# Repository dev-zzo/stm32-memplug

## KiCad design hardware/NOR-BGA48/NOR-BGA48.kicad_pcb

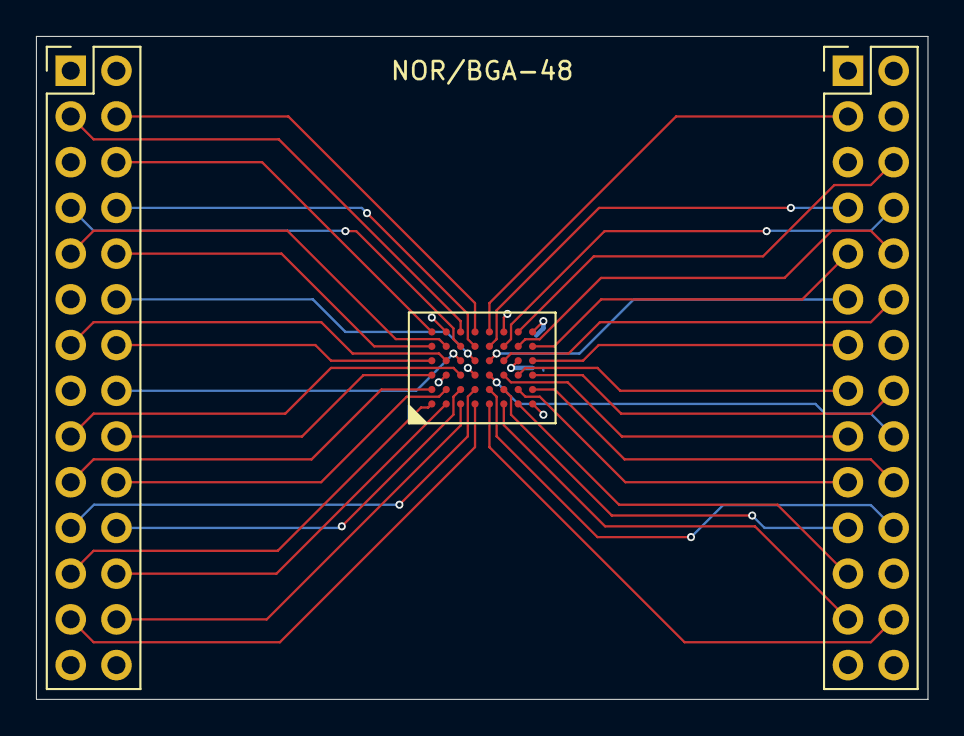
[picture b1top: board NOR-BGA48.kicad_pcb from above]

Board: 4 copper layers, 49.5 x 36.8 mm, 4 parts (1 on the bottom side), 45 nets.

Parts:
C1: 100n; C_0805_2012Metric
J1: Left; PinHeader_2x14_P2.54mm_Vertical
J2: Right; PinHeader_2x14_P2.54mm_Vertical
U1: Generic_NOR_BGA48; BGA48C80P8X6_815X615X100

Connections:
+3V3: C1.1, J2.14, J2.28, U1.B3, U1.F6, U1.G4
A0: J2.26, U1.E1
A1: J1.25, U1.D1
A2: J1.26, U1.C1
A3: J1.23, U1.A1
A4: J1.24, U1.B1
A5: J1.21, U1.D2
A6: J1.22, U1.C2
A7: J1.19, U1.A2
A8: J1.9, U1.B5
A9: J1.10, U1.A5
A10: J1.7, U1.C5
A11: J1.8, U1.D5
A12: J1.5, U1.B6
A13: J1.6, U1.A6
A14: J1.3, U1.C6
A15: J1.4, U1.D6
A16: J2.3, U1.E6
A17: J1.20, U1.B2
A18: J1.17, U1.C3
A19: J1.12, U1.D4
A20: J1.11, U1.D3
A21: J1.16, U1.C4
DQ0: J2.22, U1.E2
DQ1: J2.20, U1.H2
DQ2: J2.18, U1.E3
DQ3: J2.16, U1.H3
DQ4: J2.13, U1.H4
DQ5: J2.11, U1.E4
DQ6: J2.9, U1.H5
DQ7: J2.7, U1.E5
DQ8: J2.21, U1.F2
DQ9: J2.19, U1.G2
DQ10: J2.17, U1.F3
DQ11: J2.15, U1.G3
DQ12: J2.12, U1.F4
DQ13: J2.10, U1.G5
DQ14: J2.8, U1.F5
DQ15: J2.6, U1.G6
GND: C1.2, J2.5, J2.24, U1.H1, U1.H6
R~B: J1.18, U1.A3
~CE: J2.25, U1.F1
~OE: J2.23, U1.G1
~RST: J1.13, U1.B4
~WE: J1.14, U1.A4

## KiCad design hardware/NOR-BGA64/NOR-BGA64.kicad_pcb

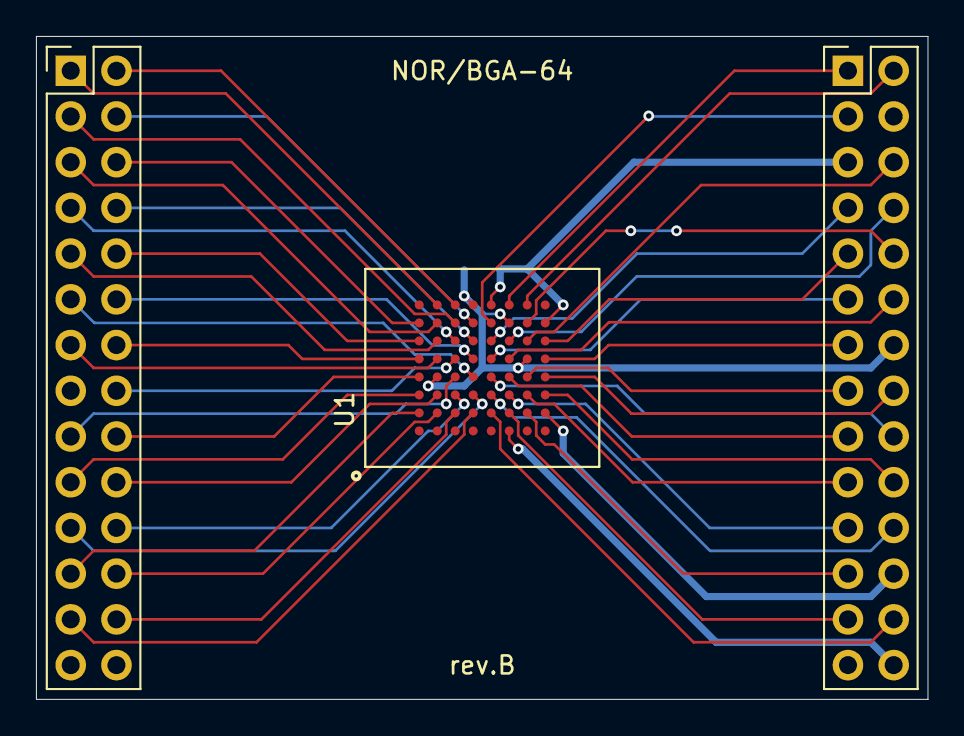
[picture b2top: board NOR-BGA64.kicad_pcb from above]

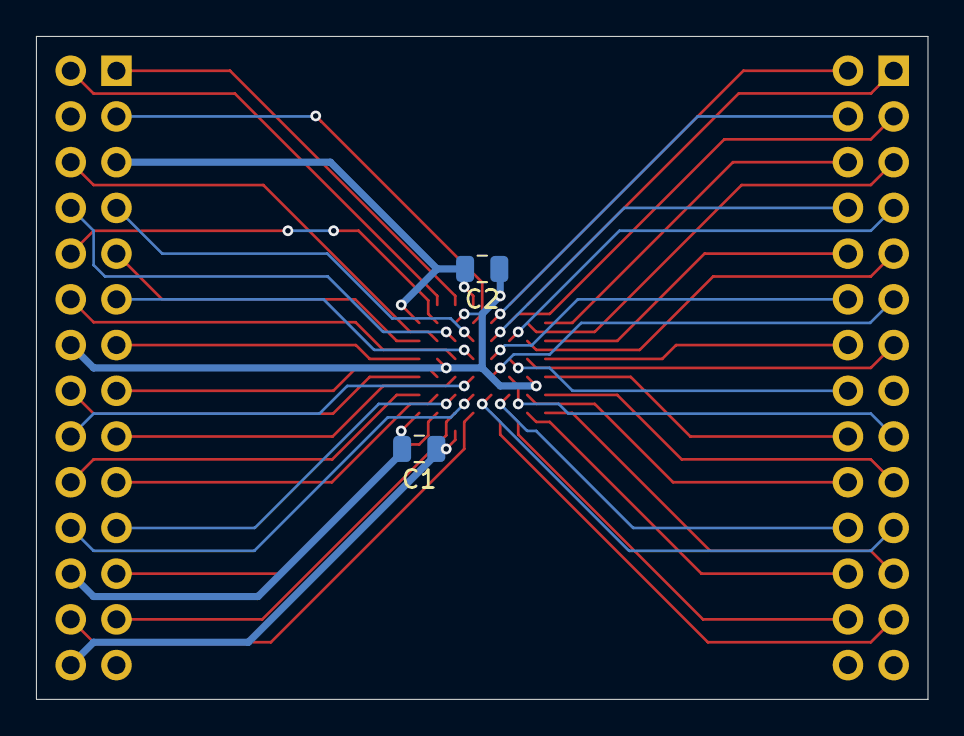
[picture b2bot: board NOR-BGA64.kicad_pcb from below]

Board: 2 copper layers, 49.5 x 36.8 mm, 5 parts (2 on the bottom side), 49 nets.

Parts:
C1, C2: 100n; C_0805_2012Metric
J1: Left; PinHeader_2x14_P2.54mm_Vertical
J2: Right; PinHeader_2x14_P2.54mm_Vertical
U1: Generic_NOR_BGA64; BGA64C100P8X8_1300X1100X130N

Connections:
+3V3: C1.1, C2.1, J2.14, J2.28, U1.B4, U1.D8, U1.F1, U1.F7, U1.G5
A0: J2.26, U1.E2
A1: J1.25, U1.D2
A2: J1.26, U1.C2
A3: J1.23, U1.A2
A4: J1.24, U1.B2
A5: J1.21, U1.D3
A6: J1.22, U1.C3
A7: J1.19, U1.A3
A8: J1.9, U1.B6
A9: J1.10, U1.A6
A10: J1.7, U1.C6
A11: J1.8, U1.D6
A12: J1.5, U1.B7
A13: J1.6, U1.A7
A14: J1.3, U1.C7
A15: J1.4, U1.D7
A16: J2.3, U1.E7
A17: J1.20, U1.B3
A18: J1.17, U1.C4
A19: J1.12, U1.D5
A20: J1.11, U1.D4
A21: J1.16, U1.C5
A22: J1.1, U1.B8
A23: J1.2, U1.C8
A24: J2.1, U1.F8
A25: J2.2, U1.G8
DQ0: J2.22, U1.E3
DQ1: J2.20, U1.H3
DQ2: J2.18, U1.E4
DQ3: J2.16, U1.H4
DQ4: J2.13, U1.H5
DQ5: J2.11, U1.E5
DQ6: J2.9, U1.H6
DQ7: J2.7, U1.E6
DQ8: J2.21, U1.F3
DQ9: J2.19, U1.G3
DQ10: J2.17, U1.F4
DQ11: J2.15, U1.G4
DQ12: J2.12, U1.F5
DQ13: J2.10, U1.G6
DQ14: J2.8, U1.F6
DQ15: J2.6, U1.G7
GND: C1.2, C2.2, J2.5, J2.24, U1.E8, U1.H2, U1.H7
R~B: J1.18, U1.A4
~CE: J2.25, U1.F2
~OE: J2.23, U1.G2
~RST: J1.13, U1.B5
~WE: J1.14, U1.A5

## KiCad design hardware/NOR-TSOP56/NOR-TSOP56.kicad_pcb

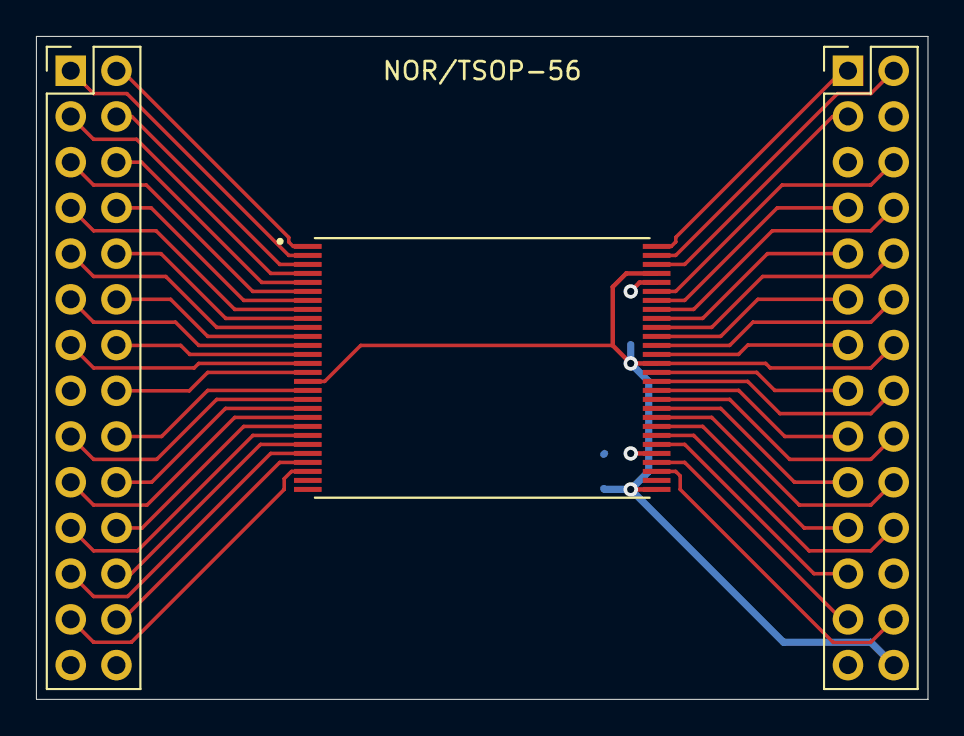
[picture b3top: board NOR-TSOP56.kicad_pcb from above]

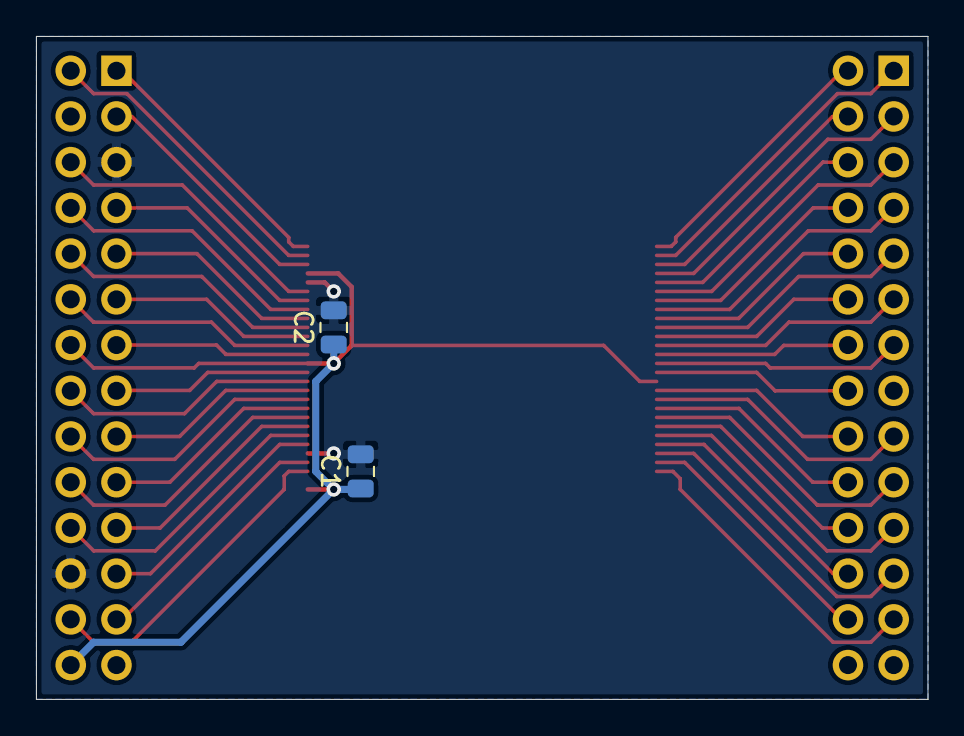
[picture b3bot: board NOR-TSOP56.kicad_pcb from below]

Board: 2 copper layers, 49.5 x 36.8 mm, 5 parts (2 on the bottom side), 49 nets.

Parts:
C1, C2: 100n; C_0805_2012Metric
J1: Left; PinHeader_2x14_P2.54mm_Vertical
J2: Right; PinHeader_2x14_P2.54mm_Vertical
U1: Generic_NOR_TSOP56; SOP50P2000X120-56N

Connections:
+3V3: C1.1, C2.1, J2.14, J2.28, U1.16, U1.29, U1.43, U1.53
A0: J2.26, U1.31
A1: J1.25, U1.26
A2: J1.26, U1.25
A3: J1.23, U1.24
A4: J1.24, U1.23
A5: J1.21, U1.22
A6: J1.22, U1.21
A7: J1.19, U1.20
A8: J1.9, U1.10
A9: J1.10, U1.9
A10: J1.7, U1.8
A11: J1.8, U1.7
A12: J1.5, U1.6
A13: J1.6, U1.5
A14: J1.3, U1.4
A15: J1.4, U1.3
A16: J2.3, U1.54
A17: J1.20, U1.19
A18: J1.17, U1.18
A19: J1.12, U1.11
A20: J1.11, U1.12
A21: J1.16, U1.15
A22: J1.1, U1.2
A23: J1.2, U1.1
A24: J2.1, U1.56
A25: J2.2, U1.55
DQ0: J2.22, U1.35
DQ1: J2.20, U1.37
DQ2: J2.18, U1.39
DQ3: J2.16, U1.41
DQ4: J2.13, U1.44
DQ5: J2.11, U1.46
DQ6: J2.9, U1.48
DQ7: J2.7, U1.50
DQ8: J2.21, U1.36
DQ9: J2.19, U1.38
DQ10: J2.17, U1.40
DQ11: J2.15, U1.42
DQ12: J2.12, U1.45
DQ13: J2.10, U1.47
DQ14: J2.8, U1.49
DQ15: J2.6, U1.51
GND: C1.2, C2.2, J2.5, J2.24, U1.33, U1.52
R~B: J1.18, U1.17
~CE: J2.25, U1.32
~OE: J2.23, U1.34
~RST: J1.13, U1.14
~WE: J1.14, U1.13

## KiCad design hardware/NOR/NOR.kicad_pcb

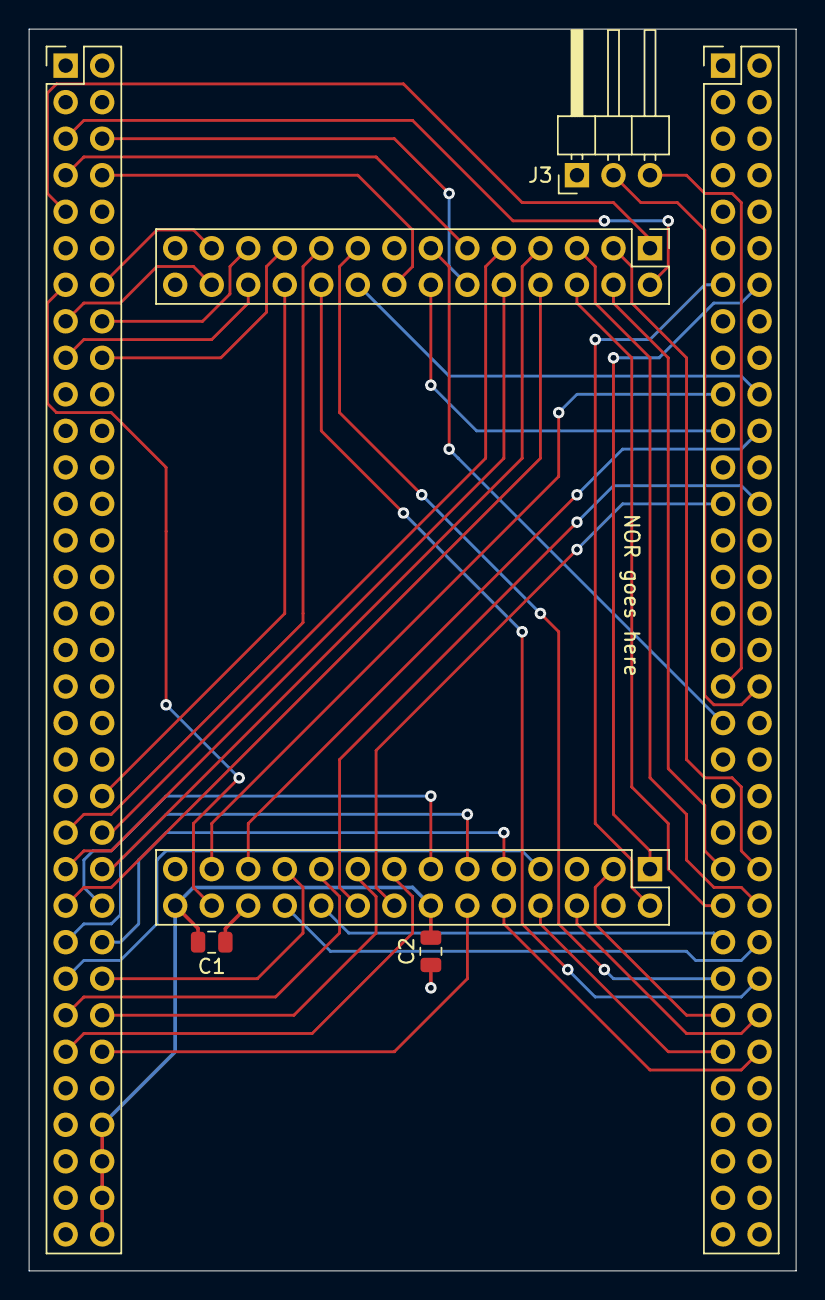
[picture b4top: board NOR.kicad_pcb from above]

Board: 2 copper layers, 53.3 x 86.4 mm, 7 parts (0 on the bottom side), 51 nets.

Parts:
C1, C2: 100n; C_0805_2012Metric
J1: Left; PinHeader_2x33_P2.54mm_Vertical
J2: Right; PinHeader_2x33_P2.54mm_Vertical
J3: DBG; PinHeader_1x03_P2.54mm_Horizontal
J4: Left; PinHeader_2x14_P2.54mm_Vertical
J5: Right; PinHeader_2x14_P2.54mm_Vertical

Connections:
+3V3: C1.2, C2.2, J1.60, J1.62, J1.64, J1.66, J5.14, J5.28
A0: J1.13, J5.26
A1: J1.14, J4.25
A2: J1.15, J4.26
A3: J1.16, J4.23
A4: J1.17, J4.24
A5: J1.18, J4.21
A6: J1.42, J4.22
A7: J1.43, J4.19
A8: J1.44, J4.9
A9: J1.45, J4.10
A10: J1.46, J4.7
A11: J1.47, J4.8
A12: J2.48, J4.5
A13: J2.47, J4.6
A14: J2.46, J4.3
A15: J2.45, J4.4
A16: J2.53, J5.3
A17: J2.52, J4.20
A18: J2.51, J4.17
A19: J1.6, J4.12
A20: J1.7, J4.11
A21: J1.8, J4.16
A22: J1.9, J4.1
A23: J1.5, J4.2
A24: J2.14, J5.1
A25: J2.13, J5.2
GND: C1.1, C2.1, J1.1, J1.2, J1.30, J1.31, J1.59, J1.61, J1.63, J1.65, J2.2, J2.4, J2.61, J2.62, J2.63, J2.64, J2.66, J3.1, J5.5, J5.24
IO0: J2.50, J5.22
IO1: J2.49, J5.20
IO2: J2.26, J5.18
IO3: J2.25, J5.16
IO4: J1.48, J5.13
IO5: J1.49, J5.11
IO6: J1.50, J5.9
IO7: J1.51, J5.7
IO8: J1.52, J5.21
IO9: J1.53, J5.19
IO10: J1.54, J5.17
IO11: J1.55, J5.15
IO12: J1.56, J5.12
IO13: J2.56, J5.10
IO14: J2.55, J5.8
IO15: J2.54, J5.6
PA9: J2.36, J3.2
PA10: J2.35, J3.3
R~B: J2.20, J4.18
~CE: J2.19, J5.25
~OE: J2.22, J5.23
~RST: J2.37, J4.13
~WE: J2.21, J4.14
